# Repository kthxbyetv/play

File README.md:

start
=====

Small, cheap and opensource TVB-Gone clone.

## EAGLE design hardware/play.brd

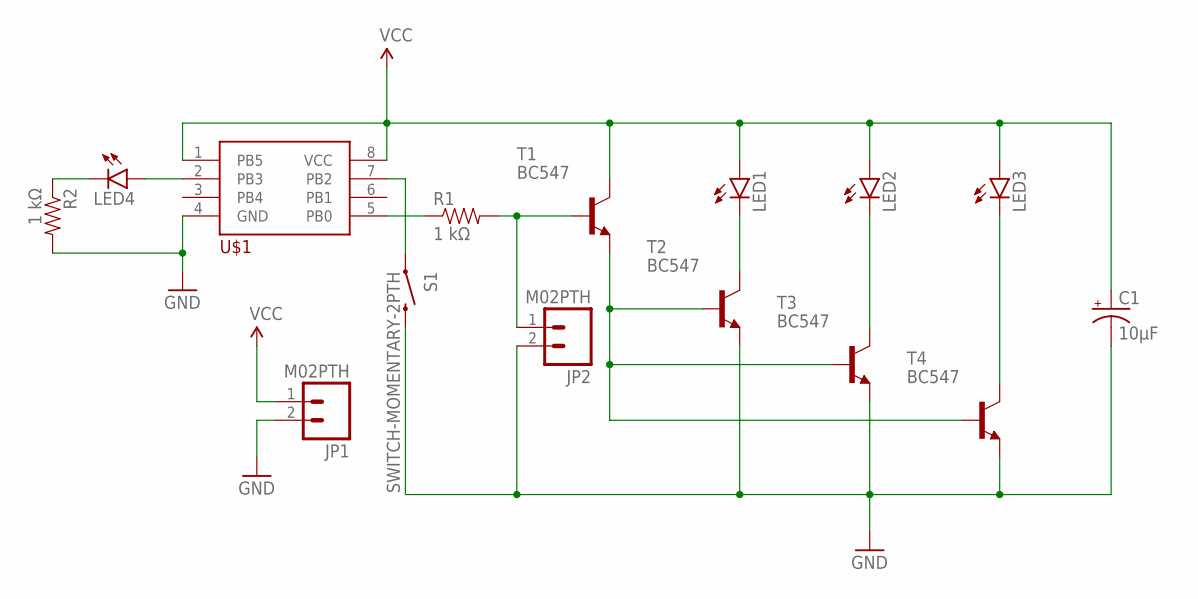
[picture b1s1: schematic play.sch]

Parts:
C1: 10µF; CPOL-RADIAL-10UF-25V
JP1, JP2: M02PTH; 1X02
LED1, LED2, LED3: LED5MM
LED4: LED3MM
R1, R2: 1 kΩ; AXIAL-0.4
S1: SWITCH-MOMENTARY-2PTH; TACTILE-PTH
T1, T2, T3, T4: BC547; TO92
U$1: ATTINY85; DIP8

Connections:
GND: C1.2 (-), JP1.2, JP2.2, R2.P$2 (2), S1.3 (2), T2.1 (E), T3.1 (E), T4.1 (E), U$1.4 (GND)
unnamed: R1.P$1 (1), U$1.5 (PB0)
unnamed: JP2.1, R1.P$2 (2), T1.2 (B)
unnamed: T1.1 (E), T2.2 (B), T3.2 (B), T4.2 (B)
unnamed: LED1.K (C), T2.3 (C)
unnamed: S1.1, U$1.7 (PB2)
unnamed: LED2.K (C), T3.3 (C)
unnamed: LED3.K (C), T4.3 (C)
unnamed: LED4.A, U$1.2 (PB3)
unnamed: LED4.K (C), R2.P$1 (1)
VCC: C1.1 (+), JP1.1, LED1.A, LED2.A, LED3.A, T1.3 (C), U$1.1 (PB5), U$1.8 (VCC)

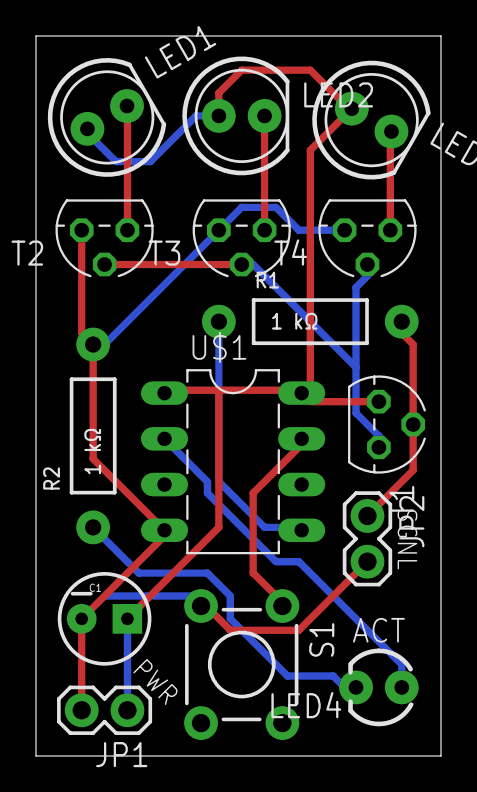
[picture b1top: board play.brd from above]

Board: 2 copper layers, 22.5 x 40.0 mm, 15 parts (0 on the bottom side), 11 nets.

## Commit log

2014-05-09 Initial schematics
2014-05-09 Moving hardware related stuff to /hardware
2014-05-09 Changing name from start to play
2014-05-10 Adding board file
2014-05-10 New board routing + ground plane
2014-05-10 Added power connector
2014-05-10 Added ACT led label
2014-05-10 Adding renderer Gerber files
2014-05-10 Fixing GERBER export problems
2014-05-10 Added smoothing cap on the schematic
2014-05-10 Updated board to add the capacitor + play logo
2014-05-10 Adding firmware section
2014-05-10 Added new rules for differents programmers
2014-05-12 New hardware PCB design, with signal connector
2014-05-12 Updated hardware
2014-05-14 Removing old gerber files, adding configuration for gerbmerge
2014-05-17 First release of non-working firmware
2014-05-17 The rest of the software
2014-05-17 Updating code
2014-05-18 Adding dev board schematics
2014-05-19 Removing old firmware files
2014-05-20 Adding Furrtek's µTVBG v5 firmware sources
2014-05-20 Removing old files
2014-05-20 Removing binary files
2014-05-20 Adding correct copyright
2014-05-20 Update gitignore file
2014-05-20 Code cleaning on xmitCodeElement (see issue #1)
2014-05-20 Code cleaning on ISR(INT0_vect) (see issue #1)
2014-05-20 Code cleaning on utils functions (see issue #1)
2014-05-20 Code cleaning on debug functions (see issue #1)
2014-05-20 Code cleaning on main (see issue #1)
2014-05-20 Removing ashes from util.h
2014-05-20 Renaming EUcodes-v4.c to codes.c (see issue #1)
2014-05-20 Cleaning Makefile (see issue #1)
2014-05-20 Cleaning code file (see issue #1)
2014-05-20 Moving pin definitions to hardware.h (see issue #1)
2014-05-21 Removing garbage form grenade mode (see issue #1)
2014-05-21 Removing garbage code from grenade mode (see issue #1)
2014-05-21 Code cleaning, moving some functions to utils. (see issue #1)
2014-05-21 Cleaning useless definitions in a_v4.h
2014-05-21 Removing unexisting function prototypes
2014-05-21 Reorganizing files (see issue #1)
2014-05-21 Misc code cleaning (see issue #1)
2014-05-21 Removing useless variable definition
2014-05-21 Bugfixed
2014-05-21 Revert old value
2014-05-31 Ajout de la fonction pour que lorsqu'on appuie à nouveau sur le bouton lors du processus, cela stoppe la diffusion des codes. En gros, le bouton fait maintenant ON/OFF au lieu de faire seulement ON.
2014-05-31 Correction de la syntaxe merdique, cela favorise une meilleure lecture. Retrait d'un commentaire inutile?
2014-05-31 Nouveau Makefile, le problème c'est que je crois qu'il est pourrave, c'est pour ça que l'ancien est sauvegardé. Sinon, modification du main (Z0MG LES POINTEURS) et amélioration de deux-trois connerie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
2014-05-31 Suppression des tables de temps inutiles et commentées, réorganisation des codes (olala, c'est plus joli).
2014-05-31 aeoaeoaeo
2014-06-01 Optimisations, substitution du reset par watchdog par une boucle, Z0MG LE POINTEUR.
2014-06-01 Suppression des virgules inutiles dans les codes
2014-06-02 Suppression des trucs inutiles
2014-06-02 Moins, voire plus du tout, de problèmes d'optimisation
2014-06-03 Makefile qui clean + delai
2014-06-03 Emplacement des projos dans la liste.
2014-06-03 Meilleur Makefile
2014-06-03 WOW le très Makefile encore oui très présentement such le Makefile.
2014-06-03 Makefile de fou.
2014-06-03 Double-click.
2014-06-03 Petits changements et réorganisations.
2014-06-03 Suppression de trucs inutiles CTB
2014-06-03 Double-click function
2014-06-03 The one click version of the firmware, if you don't like pushing buttons.
2014-06-03 The default mode is one click to stop. There is also a main.c which enables to click one time top reset and two times to power off the device.
2014-10-08 Bugfixing PCB + updating makefile

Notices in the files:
parts and their libraries:
SparkFun-Resistors: Licensing: Creative Commons ShareAlike 4.0 International - https://creativecommons.org/licenses/by-sa/4.0
